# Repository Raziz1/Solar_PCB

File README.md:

# Solar Power Management PCB ☀️
The following project is a power management PCB designed to charge a lithium-ion battery using a solar panel and discharge it into an Arduino for low-power applications.

<p align="center"><i>Blender Render</i></p>

## Arduino Low-Power Application 🔋
Before diving into the PCB design I am going to explore the low-power application that I have designed for this project. The application [Full_Functionality.ino](./Arduino_Code/Full_Functionality/Full_Functionality.ino) utilizes the [DHT11 sensor](https://www.arduino.cc/reference/en/libraries/dht11/) to record temperature and humidity readings, then writes them to the onboard EEPROM (1 KB). Once the data has been stored in the EEPROM the arduino goes into a lower power state by utilizing the [narcoleptic library](https://github.com/brabl2/narcoleptic). I am running this entire application on an [Arduino Uno REV3](https://docs.arduino.cc/hardware/uno-rev3/#tech-specs).

For this application, I would like the Arduino to last as long as possible on battery power. To reduce it's power consumption I referenced the following two articles: [The Arduino Guide to Low Power Design](https://docs.arduino.cc/learn/electronics/low-power/), [Arduino minimal power usage](https://arduino.stackexchange.com/questions/21616/arduino-minimal-power-usage), and [Power saving techniques for microprocessors
](https://www.gammon.com.au/power). A lot of the common techniques involved disabling unused peripherals, reducing clock speeds, and forcing the CPU into a low power mode. One extremely effective method that <b>I did not</b> attempt was utilizing a "bare bones" Atmega328 board. By stripping away a lot of unnecessary components (i.e. USB controller, LDO, etc...) you can significantly reduce the power consumption.

## Arduino Pin-out

| **Arduino** | **DHT11** |
| ------------- | ------------- |
| 5V            | VCC           | 
| GND           | GND           |   
| 2/PD2         | DATA          | 

<br>

<p align="center"><i>Arduino Pin-out</i></p>

## Power Consumption Tests 🪫
To test the power consumption of the Arduino, I used a bench power supply, a 100-ohm shunt resistor, and the Analog Discovery 2 USB oscilloscope.

### Default Sketch
For the first test I had the Arduino running the default sketch as seen below.
```C++
void setup () {}
void loop () {}
```
The current consumption was measured at two supply voltage levels: 12V and 8V. Realistically, for our application, we will be running the Arduino off 8V through the barrel connector.
* 12V - 44.17mA
* 8V - 25.07mA

<p align="center"><i>Current Draw 12V [LEFT] vs 8V [RIGHT]</i></p>

### Low_Power_Sketch.ino
The Low_Power_Sketch.ino utilizes the sleep, wdt, and power library to lower the Arduino's power consumption. To lower the Arduino's power consumption I did the following:

* Desoldered the 5V 'ON' LED
* Disabled USER LED 13
* Disabled ADC
* Changing the clock pre-scalar had no effect on the power consumption so I left it as 1.
* Disabled all peripheral modules (SERIAL, ADC, SPI, USART, TIMER 0, TIMER 1, TIMER 2, I2C)
* Disabled brown-out feature. Brownout detection is a hardware feature that shuts down the processor if the system voltage is below a threshold
* Put the CPU into [SLEEP_MODE_PWR_DOWN](https://onlinedocs.microchip.com/pr/GUID-A834D554-5741-41A3-B5E1-35ED7CD8250A-en-US-5/index.html?GUID-825A28EE-C4E4-4C03-864F-92AA9BA41231). The Microchip web page explains what occurs during this mode.

The resulting current consumptions was:
* 8V - 18.78mA

<p align="center"><i>Current Draw Low_Power_Sketch.ino</i></p>

### Narcoleptic_Sketch.ino
The Narcoleptic_Sketch.ino uses many of the same techniques as the above sketch; however, this script utilizes the [Narcoleptic library](https://github.com/brabl2/narcoleptic) to achieve its low power consumption. The following techniques were used:

* Desoldered the 5V 'ON' LED
* Disabled USER LED 13
* Disabled ADC
* Changing the clock pre-scalar had no effect on the power consumption so I left it as 1.
* Disabled all peripheral modules (SERIAL, ADC, SPI, USART, TIMER 0, TIMER 1, TIMER 2, I2C)
* Disabled brown-out feature. Brownout detection is a hardware feature that shuts down the processor if the system voltage is below a threshold
* Narcoleptic.Delay(x_milliseconds) is called to force the CPU in a low-power state for x_milliseconds.

The resulting current consumptions was:
* 8V - 18.27mA

<p align="center"><i>Current Draw Narcoleptic_Sketch.ino</i></p>

### Full_Functionality.ino
The Full_Functionality.ino sketch is the main program that performs the tasks described in the introduction while using the low power modes that were used in Narcoleptic_Sketch.ino. 

The resulting current consumptions was:
* Awake mode (8V) - 22.42mA
* Low power mode (8V) - 18.30mA

<p align="center"><i>Full_Functionality.ino Low power mode [LEFT] vs Awake mode [RIGHT]</i></p>

### Future Power Consumption Improvements
Despite the power savings documented above, there are still quite a few methods that were left out during this process, which can yield large power savings.

* The first method is extensively discussed in the [Power saving techniques for microprocessors](https://www.gammon.com.au/power) article. You can strip various unnecessary parts from the Arduino, leaving you with a bare-bones version of the board. This includes the voltage regulators (for +5V and +3.3V), USB interface chip (for the USB port), and the "power" LED. According to the article, this resulted in a current consumption of 360uA!
    * The Arduino Uno Rev 3 uses the NCP1117ST50T3G as it's 5V linear voltage regulator. This regulator has a quiescent current of 10mA! If you bypass the LDO you can avoid wasting power.
* Secondly, the ATmega328P MCU can be run at lower frequencies and hence a lower voltage which can reduce the boards power consumption

## Power Management Components ⚡
Now that we know the power consumption of the Arduino, we can begin picking components for this project. This section will focus on the choice of solar panel and lithium-ion battery.

### Lithium Ion Battery 🔋
For the battery, I ended up selecting a pair of lithium-ion batteries I already had at home. The batteries were two 3.7V 2600mAh lithium-ion batteries from PKCELL. The batteries were arranged in series in a battery pack to produce an output voltage of 7.4V and a capacity of 2600 mAh. [Li-ion Battery ICR18650 2600mAh 3.7V Datasheet](https://www.parts-express.com/pedocs/specs/142-202--pkcell-flat-top-18650-li-ion-3.7v-2600mah-rechargeable-battery-spec-sheet.pdf). Some important specifications to note about this battery are the following:
* Nominal Voltage - 3.7V
* Charging Cut-off Voltage - 4.2V
* Discharge Cut-off Voltage - 3.0V
* Standard Charge - Constant Current 0.5C Constant Voltage 4.2V 0.01 C cut-off
* Standard Discharge - Discharge at 0.2 C to 3.0V

<p align="center"><i>PKCELL Lithium Ion Batteries</i></p>

#### Arduino Low-Power Application Discharge Rate
Now that we know the battery capacity and the Arduino's current consumption, we can determine the lifespan of the battery while supplying the Arduino.

| **Variable**  | **Description**           | **Value** |
| ------------- | -------------             | --------- |
| C             | Battery Capacity          | 2600 mAh  | 
| Is            | Current while sleeping    | 18.3mA    |
| Ia            | Current while awake       | 22.4mA    |
| Wph           | # of wakeups per hour     | 1         |
| Wt            | Duration of a single wake | 1s        |

Time awake per hour: ${Twph=Wph\cdot Wt=1s}$

Time asleep per hour: ${Tsph=msph-Wtph=3599s}$

Average current draw: ${Iavg=\left(\left(Ia\cdot Twph\right)+\left(Is\cdot Tsph\right)\right)/3600s=18.3011\thinspace mA}$

Life of battery: ${\frac{C}{I_{avg}}=\frac{2600mAh}{18.3011mA}=142.067\thinspace hours=5.919\thinspace days}$

Alternatively, you could use this [Battery Life Calculator](https://oregonembedded.com/batterycalc.htm), which includes the self-discharge rate of a battery in its calculations. Based on this calculator, the battery's life ends up being 5.03 days.

### Solar Panel 🔆
To increase the lifespan of the battery, you could further decrease the current consumption of the Arduino using the previously mentioned methods, or you could hook up a solar panel to recharge the batteries.

After a bit of searching I was able to find a 12V 4.2W (350mA Max) portable [solar panel module](https://www.amazon.ca/Portable-Polysilicon-Battery-Charger-Efficiency/dp/B07S1P67HL/ref=sr_1_97_sspa?crid=2WAO18NW0X2GN&dib=eyJ2IjoiMSJ9.fZVIoLELaw3YZhhkogK5VGuvzYc6wwH_Px50gEwUL5AK6Nxr_yeX3NtH-g3Q1hlIK30yAnZ0evMQHhDVoLYAm4sbS6SBN7zU1qKFeF3U7BU.zWxxjvWhspQamoYMqpsdiUn7VfXNYG4ixH8fwb_Tuoc&dib_tag=se&keywords=solar+cell&qid=1717475335&s=hi&sprefix=solar+ceil%2Ctools%2C96&sr=1-97-spons&sp_csd=d2lkZ2V0TmFtZT1zcF9hdGZfbmV4dA&psc=1).

#### Ideal Conditions
If we assume ideal conditions where the sun is visible 100% of the day we can determine how long it would take for the solar panel to recharge the battery. 
* ${t}$ is the time (in hours) it takes to charge the battery
* ${Q}$ is the capacity of the battery (in mAh), which is 2600mAh in our case
* ${I}$ is the current (in mA) that the panel can supply, which in our case is 350mA max.

${t=\frac{Q}{I}=\frac{2600}{350}=7.42\thinspace hours}$

#### Real World Conditions
For real-world conditions, we can assume that the total hourly power is closer to 50% of the solar panel's maximum power (175mA). Additionally, we can include the power consumption of the Arduino, which is around 18.3mA.
* ${t}$ is the time (in hours) it takes to charge the battery
* ${Q}$ is the capacity of the battery (in mAh), which is 2600mAh in our case
* ${Iload}$ is the net current (in mA) that the Arduino is drawing, which is 18.3mA in our case
* ${Isolar}$ is the net current (in mA) that the solar panel is providing, which is 175mA in our case. 

${I_{net}=I_{solar}-I_{net}=175\thinspace mA-18.3\thinspace mA=156.7\thinspace mA}$

${t=\frac{Q}{I_{net}}=\frac{2600}{156.7}=16.6\thinspace hours}$

## Battery Management IC 🔌
The battery management IC being used in this project is the [LT3652](https://www.analog.com/en/products/lt3652.html)

* The LT3652 is a complete monolithic step-down battery charger designed for solar power and capable of supporting multi-chemistry, multi-cell batteries.
* Input Supply Voltage Regulation Loop for MPPT Solar Applications
* Wide Input Voltage Range: 4.95V to 32V (40V Abs Max)
* Programmable Charge Rate: Up to 2A
* User-Selectable Termination: C/10 or On-Board Termination Timer
* Resistor Programmable Float Voltage: Up to 14.4V
* Accommodates Li-Ion/Polymer, LiFePO4, SLA Chemistries
* The primary reason for choosing this IC was because a simulation model for it is available in LTspice.

## Design Notes
- [x] VIN Input Supply
- [x] Charge Current Programming
- [x] BOOST Supply
- [x] VIN/BOOST Start-Up Requirement
- [x] VBAT Output Decoupling
- [x] Inductor Selection
- [x] Rectifier Selection
- [x] Battery Float Voltage Programming
- [x] Input Supply Voltage Regulation
- [x] Battery Voltage Temperature Compensation
- [x] Status Pins
- [x] C/10 Termination

### VIN Input Supply
* A high-quality, low ESR decoupling capacitor is recommended to minimize voltage glitches on VIN

#### RMS Ripple Current
${I_{CVIN\left(RMS\right)}≅I_{CHG\left(MAX\right)}•\left(V_{BAT}/V_{IN}\right)•\left(\left[V_{IN}/V_{BAT}\right]-1\right)^{\frac{1}{2}}}$

${I_{CVIN\left(RMS\right)}=0.5\cdot \left(\frac{7.4}{12}\right)\cdot \left(\left(\frac{12}{7.4}\right)-1\right)^{\frac{1}{2}}=0.19447\thinspace A}$

* where ${I_{CHG\left(MAX\right)}}$ is the maximum average charge current
(100mV/ ${R_{SENSE}}$ ).
* The simple worst-case of ½ • ${I_{CHG\left(MAX\right)}}$ is commonly
used for design.
* Ripple current in capacitors is crucial to consider because it directly impacts the component's performance, reliability, and lifespan by causing internal heating and potential degradation

#### Input Ripple Voltage
Bulk capacitance is a function of desired input ripple voltage (ΔVIN), and follows the relation:
${C_{IN{\left(BULK\right)}}=I_{CHG{\left(MAX\right)}}•\left(V_{BAT}/V_{IN}\right)/∆V_{IN}\thinspace \left(µF\right)}$

${C_{IN\left(BULK\right)}=0.4\cdot \frac{\left(\frac{7.4}{12}\right)}{0.1}=2.46\thinspace uF}$

* Input ripple voltages above 0.1V are not recommended. 10µF is typically adequate for most charger applications.

### Charge Current Programming
The data sheet describes the charge current programming as follows: <i>"The LT3652 charger is configurable to charge at average currents as high as 2A. Maximum charge current is set by choosing an inductor sense resistor (RSENSE)..."</i> 

${R_{SENSE}\thinspace = \thinspace 0.1/I_{CHG\left(MAX\right)}}$

The maximum charging current is limited by the maximum current output of the solar panel, which is 350 mA. Therefore, we can set the limit to 400 mA to allow for some headroom.

${R_{SENSE}\thinspace = \thinspace 0.1/I_{CHG\left(MAX\right)}=0.1/0.4=0.25Ω}$

### BOOST Supply
The voltage on the decoupling capacitor is refreshed through a diode, with the anode connected to either the battery output voltage or an external source, and the cathode connected to the BOOST pin. Rate the diode average current greater than 0.1A, and reverse voltage greater than VIN(MAX).

### VIN/BOOST Start-Up Requirement
When an LT3652 charger is not switching, the SW pin is
at the same potential as the battery, which can be as high
as VBAT(FLT). As such, for reliable start-up, the VIN supply
must be at least 3.3V above VBAT(FLT). Once switching
begins and the BOOST supply capacitor gets charged
such that (VBOOST – VSW) > 2V, the VIN requirement no
longer applies.

### VBAT Output Decoupling
An LT3652 charger output requires bypass capacitance connected from the BAT pin to ground (CBAT). A 10µF ceramic capacitor is required for all applications.
* If it is desired to operate a system load from the LT3652 charger output when the battery is disconnected, additional bypass capacitance is required. In this type of application, excessive ripple and/or low amplitude oscillations can occur without additional output bulk capacitance. For these applications, place a 100µF low ESR non-ceramic capacitor (chip tantalum or organic semiconductor capacitors such as Sanyo OS-CONs or POSCAPs) from BAT to ground, in parallel with the 10µF ceramic bypass capacitor. This additional bypass capacitance may also be required in systems where the battery is connected to the charger with long wires. The voltage rating of CBAT must meet or exceed the battery float voltage.

### Inductor Selection
The primary criterion for inductor value selection in an LT3652 charger is the ripple current created in that inductor.
* Once the inductance value is determined, an inductor must also have a saturation current equal to or exceeding the maximum peak current in the inductor
* ${L=\frac{10•R_{SENSE}}{\frac{ΔI_L}{I_{CHG\left(MAX\right)}}}•V_{BAT\left(FLT\right)}•\left(1-\frac{V_{BAT\left(FLT\right)}}{V_{IN\left(MAX\right)}}\right)\thinspace \left(µH\right)}$
    * ${L=\frac{10\cdot 0.2}{\frac{0.12}{0.4}}\cdot 7.4\cdot \left(1-\frac{7.4}{12}\right)=23.64\thinspace uH}$    
* In the above relation, VIN(MAX) is the maximum operational voltage. Ripple current is typically set within a range of 25% to 35% of ICHG(MAX), so an inductor value can be determined by setting 0.25 < ΔIL/ICHG(MAX) < 0.35
* Magnetics vendors typically specify inductors with maximum RMS and saturation current ratings. Select an inductor that has a saturation current rating at or above ${\left(1+ΔI_{MAX}/2\right)•I_{CHG\left(MAX\right)}}$, and an RMS rating above ${I_{CHG\left(MAX\right)}}$.
* Inductors must also meet a maximum voltsecond product requirement. If this specification is not in the data sheet of an inductor, consult the vendor to make sure the maximum volt-second product is not being exceeded by your design. The minimum required volt-second product is: ${V_{BAT\left(FLT\right)}•\left(\frac{1-V_{BAT\left(FLT\right)}}{V_{IN\left(MAX\right)}}\right)\left(V•\thinspace µS\right)}$

### Rectifier Selection
The rectifier diode from SW to GND, in a LT3652 battery charger provides a current path for the inductor current when the main power switch is disabled. The rectifier is selected based upon forward voltage, reverse voltage, and maximum current. A Schottky diode is required, as low forward voltage yields the lowest power loss and highest efficiency. The rectifier diode must be rated to withstand reverse voltages greater than the maximum VIN voltage.

The minimum average diode current rating (${I_{DIODE\left(MAX\right)}}$)
is calculated with maximum output current (${I_{CHG\left(MAX\right)}}$),
maximum operational VIN, and output at the precondition
threshold (${V_{BAT\left(PRE\right)},\thinspace or\thinspace 0.7•V_{BAT\left(FLT\right)}}$): ${I_{DIODE\left(MAX\right)}>I_{CHG\left(MAX\right)}•\frac{V_{IN\left(MAX\right)}-V_{BAT\left(PRE\right)}}{V_{IN\left(MAX\right)}}\left(A\right)}$

${I_{DIODE\left(MAX\right)}>0.4\cdot \frac{12-5.18}{12}}$

${I_{DIODE\left(MAX\right)}>0.2273\thinspace A}$

### Battery Float Voltage Programming
The output battery float voltage (VBAT(FLT)) is programmed by connecting a resistor divider from the BAT pin to VFB. VBAT(FLT) can be programmed up to 14.4V.

Using a resistor divider with an equivalent input resistance at the VFB pin of 250k compensates for input bias current error. Required resistor values to program desired VBAT(FLT) follow the equations:
* ${R_{FB1}=\left(V_{BAT\left(FLT\right)}•2.5•10^5\right)/3.3\thinspace \left(Ω\right)}$
* ${R_{FB2}=\left(R_{FB1}•\left(2.5•10^5\right)\right)/\left(R_{FB1}-\left(2.5•10^5\right)\right)\thinspace \left(Ω\right)}$ 

The charge function operates to achieve the final float voltage of 3.3V on the VFB pin. The auto-restart feature initiates a new charging cycle when the voltage at the VFB pin falls 2.5% below that float voltage. Because the battery voltage is across the VBAT(FLT) programming resistor divider, this divider will draw a small amount of current from the battery (IRFB) at a rate of: IRFB = 3.3/RFB2

Precision resistors in high values may be hard to obtain, so for some lower VBAT(FLT) applications, it may be desirable to use smaller-value feedback resistors with an additional resistor (RFB3) to achieve the required 250k equivalent resistance. The resulting 3-resistor network, as shown in Figure 5, can ease component selection and/or increase output voltage precision, at the expense of additional current through the feedback divider.

${\frac{R_{FB2}}{R_{FB1}}=\frac{3.3}{\left(V_{BAT\left(FLT\right)}-3.3\right)}}$

${\frac{R_{FB2}}{R_{FB1}}=\frac{3.3}{\left(7.4-3.3\right)}=0.80487}$

Set the divider current (IRFB) = 10uA yields:

${R_{FB2}=\frac{3.3}{10uA}=330k}$

Solving for RFB1:

${R_{FB1}=\frac{330k}{0.80487}=410k}$

The divider equivalent resistance is:

${R_{FB1}||R_{FB2}=182.8k}$

To satisfy the 250k equivalent resistance to the VFB pin: 

${R_{FB3}=250k-182.8k=67.2k}$

Because the VFB pin is a relatively high impedance node, stray capacitances at this pin must be minimized. Special attention should be given to any stray capacitances that
can couple external signals onto the pin, which can produce undesirable output transients or ripple. Effects of parasitic capacitance can typically be reduced by adding
a small-value (20pF to 50pF) feed forward capacitor from the BAT pin to the VFB pin

### Input Supply Voltage Regulation

The LT3652 contains a voltage monitor pin that enables programming a minimum operational voltage. Connecting a resistor divider from VIN to the VIN_REG pin enables programming of minimum input supply voltage, typically used to program the peak power voltage for a solar panel. Maximum charge current is reduced when the VIN_REG pin is below the regulation threshold of 2.7V. If an input supply cannot provide enough power to satisfy
the requirements of an LT3652 charger, the supply voltage will collapse. A minimum operating supply voltage can thus be programmed by monitoring the supply through a resistor divider, such that the desired minimum voltage corresponds to 2.7V at the VIN_REG pin. The LT3652 servos the maximum output charge current to maintain
the voltage on VIN_REG at or above 2.7V. Programming of the desired minimum voltage is accomplished by connecting a resistor divider as shown in
Figure 6. The ratio of RIN1/RIN2 for a desired minimum voltage (VIN(MIN)) is:

${\frac{R_{IN1}}{R_{IN2}}=\left(\frac{V_{IN\left(MIN\right)}}{2.7}\right)-1}$

If the voltage regulation feature is not used, connect the VIN_REG pin to VIN.

For my configuration I will set the ${V_{IN\left(MIN\right)}}$ as 10V 

${\frac{R_{IN1}}{R_{IN2}}=\frac{10}{2.7}-1=2.7037}$

${R_{IN1}=270k}$

${R_{IN2}=100k}$

### MPPT Temperature Compensation

### Battery Voltage Temperature Compensation

<i>See Page 16 of the datasheet for MPPT temperature compensation and battery voltage temperature compensation</i>

In this design I opted to ignore the following features to simplify the design. Nevertheless, these features are actually very easy to work with and are well documented within the datasheet.

### Status Pins

The LT3652 reports charger status through two open collector outputs, the CHRG and FAULT pins. These pins can accept voltages as high as VIN, and can sink up to 10mA when enabled. The CHRG pin indicates that the charger is delivering current at greater that a C/10 rate, or 1/10th of the programmed maximum charge current. The FAULT pin signals bad battery and NTC faults.

If the battery is removed from an LT3652 charger that is configured for C/10 termination, a sawtooth waveform of approximately 100mV appears at the charger output, due to cycling between termination and recharge events, This cycling results in pulsing at the CHRG output. An LED connected to this pin will exhibit a blinking pattern, indicating to the user that a battery is not present. The frequency of this blinking pattern is dependent on the output capacitance.

<p align="center"><i>Status Pins Table</i></p>

### C/10 Termination

The LT3652 supports a low-current based termination scheme, where a battery charge cycle terminates when the current output from the charger falls to below one-tenth of the maximum current, as programmed with RSENSE. The C/10 threshold current corresponds to 10mV across RSENSE. This termination mode is engaged by shorting the TIMER pin to ground.
When C/10 termination is used, a LT3652 charger will source battery charge current as long as the average current level remains above the C/10 threshold. As the full-charge float voltage is achieved, the charge current falls until the C/10 threshold is reached, at which time the charger terminates and the LT3652 enters standby mode. The CHRG status pin follows the charger cycle, and is high impedance when the charger is not actively charging. When VBAT drops below 97.5% of the full-charged float voltage, whether by battery loading or replacement of the battery, the charger automatically re-engages and starts charging. There is no provision for bad battery detection if C/10 termination is used.

## Thermal Consideration 🔥
A schottky diode is placed at the output of a solar panel primarily to prevent reverse current flow, which can discharge the battery at night or during low-light conditions. For this schottky diode I had originally chosen the [B5817WS-TP](https://www.digikey.com/en/products/detail/micro-commercial-co/B5817WS-TP/2213553). One thing to consider is the thermal performance of this diode. 

According to the datasheet, we expect this to operate with an average forward voltage drop of 0.45V. We also expect it to sink 350mA at the solar panel's peak performance.

${P=V\cdot I=0.45\cdot 0.350=0.1575\ Watts}$

According to the datasheet the maximum thermal resistance is 500°C/W from junction to ambient. Therefore we would expect the diode to rise above ambient temperature by:

${T=500°C/W\cdot 0.1575W=78.75°C}$

While this is technically within the operating specifications of the diode, it would be wise to consider a diode with superior thermal performance to prevent potential thermal runaway.

As such, a suitable alternative with a slightly larger case size would be the [SMD22PL-TP](https://www.digikey.ca/en/products/detail/micro-commercial-co/SMD22PL-TP/1793265). By using the same calculations as above, we can expect the following power dissipation:

${P=V\cdot I=0.5\cdot 0.350=0.175\ Watts}$

${T=115°C/W\cdot 0.175W=20.125°C}$

## Simulation

<p align="center"><i>LTSpice Schematic Capture</i></p>

<p align="center"><i>LTSpice Charge Simulation 0% --> 100% (Vin vs Vout)</i></p>

<p align="center"><i>LTSpice CHG LED Status</i></p>

### Layout Considerations
* The switch node (Pin SW) trace should be kept as short as possible to minimize high frequency noise.
* The input capacitor (CIN) should be placed close to the IC to minimize this switching noise.
* Short, wide traces on these nodes also help to avoid voltage stress from inductive ringing.
* The BOOST decoupling capacitor should also be in close proximity to the IC to minimize inductive ringing.
* The SENSE and BAT traces should be routed together, and these and the VFB trace should be kept as short as possible. Shielding these signals from switching noise with a ground plane is recommended.
* High current paths and transients should be kept isolated from battery ground, to assure an accurate output voltage reference.
* The LT3652 packaging has been designed to efficiently remove heat from the IC via the Exposed Pad on the backside of the package, which is soldered to a copper footprint on the PCB. This footprint should be made as large as possible to reduce the thermal resistance of the IC case to ambient air.

<p align="center"><i>Layout power loops</i></p>

## PCB Design

<p align="center"><i>Schematic Design</i></p>

<p align="center"><i>PCB Design</i></p>

### Design Choices
* I have incorporated 6 vias beneath the ground pad of the LT3652, connecting to the bottom layer ground plane. This design choice aims to improve thermal dissipation by effectively transferring heat away from the chip and to the lower ground plane.
* I have placed grounded via stitching all along the edge of the board to achieve multiple benefits: reducing electromagnetic emissions by containing radially propagating waves, improving shielding to protect internal circuitry from external interference, and enhancing ground connectivity by linking ground planes across different layers, thereby ensuring efficient current return paths and low impedance. 
* Via stitching has been strategically applied around traces and components associated with high-frequency switching nodes, along with sensitive feedback lines. This technique is known as shielding and helps prevent the coupling of EM waves into stray traces in two ways: The loop inductance in the via region is lower because the via is closer to ground. Being closer to ground causes the signal via/ground via transition to dominate the total capacitance experienced along the via. 
    * You can calculate the maximum frequency that a given array of stitching vias will shield against based on their spacing. ${f_{max}=\frac{c}{8\cdot \:s\cdot \sqrt{ε_r}}=\frac{299792458}{8\:\cdot \:0.002\cdot \sqrt{4.4}}=8.93GHz}$
        * (c) - The speed of light 299792458 m/s
        * (s) - The spacing between Via's
        * (ε) - relative permittivity (εr) of the PCB material. For FR-4 ≈ 4.4

<p align="center"><i>Layout power loops</i></p>

## Final BOM 📃
* 2× [ICR18650 2600mAh 3.7V by PKCELL](https://www.batterypkcell.com/pkcell-18650-3-7v-2200mah-new-rechargeable-lithium-battery-product/)
* [12V 4.2W Solar Panel Module](https://www.amazon.ca/Portable-Polysilicon-Battery-Charger-Efficiency/dp/B07S1P67HL/ref=sr_1_97_sspa?crid=2WAO18NW0X2GN&dib=eyJ2IjoiMSJ9.fZVIoLELaw3YZhhkogK5VGuvzYc6wwH_Px50gEwUL5AK6Nxr_yeX3NtH-g3Q1hlIK30yAnZ0evMQHhDVoLYAm4sbS6SBN7zU1qKFeF3U7BU.zWxxjvWhspQamoYMqpsdiUn7VfXNYG4ixH8fwb_Tuoc&dib_tag=se&keywords=solar+cell&qid=1717475335&s=hi&sprefix=solar+ceil%2Ctools%2C96&sr=1-97-spons&sp_csd=d2lkZ2V0TmFtZT1zcF9hdGZfbmV4dA&psc=1)
* [Renogy 10 Watt 12 Volt Monocrystalline Solar Panel](https://www.amazon.ca/Renogy-Monocrystalline-Compact-Sprinkler-Applications/dp/B084MGS7KC/ref=mp_s_a_1_3?dib=eyJ2IjoiMSJ9.c6Ibopwzdw26-vXq0iM-t1X8KARw0PDHBEDa3QlSnucRRHnDQTm4tTqQhkWwJL5nBQfEcQG8s4SG3f0IUzD3oGxv7BOgHw_WdngOzWXWF6KB_JtXohbMmgxpaDqCVNrzySHuhJVVXBAElseQOjCSJATDCa9YTwj-vGisQsCN-2uRbedcTW2VFvSyFnXtX7MV--3pARRPw2olqf5FF4tQuw.rWuqIR5JHi2lb0LAExF7YcRQJTtzPzDO3Edo9STDuG8&dib_tag=se&keywords=10%2Bwatt%2Bsolar%2Bpanel&qid=1720388517&sr=8-3&th=1) (More powerful solar panel alternative)
    * [Datasheet](https://ca.renogy.com/content/renogy-day-2023/RNG-10D-SS-G1Datasheet.pdf)
    * Optimum Operating Voltage - 18V
    * Optimum Operating Current - 0.56A
* [LT3652EMSE#TRPBF - IC BATT CHG MULTI-CHEM 12MSOP](https://www.digikey.ca/en/products/detail/analog-devices-inc/LT3652EMSE-TRPBF/7838158)
* 1× [B5817WS-TP - DIODE SCHOTTKY 20V 1A SOD323](https://www.digikey.com/en/products/detail/micro-commercial-co/B5817WS-TP/2213553)
* 1× [SS2P2-M3/84A - Diode 20 V 2A Surface Mount DO-220AA (SMP)](https://www.digikey.ca/en/products/detail/vishay-general-semiconductor-diodes-division/SS2P2-M3-84A/1091548)
* 1× [MBRS340T3G - DIODE SCHOTTKY 40V 3A SMC](https://www.digikey.com/en/products/detail/onsemi/MBRS340T3G/918009)
* 2× [150060VS75000 - LED GREEN CLEAR 0603 SMD](https://www.digikey.ca/en/products/detail/w%C3%BCrth-elektronik/150060VS75000/4489906)
* 2× [ERJ-3EKF1101V - RES SMD 1.1K OHM 1% 1/10W 0603](https://www.digikey.ca/en/products/detail/panasonic-electronic-components/ERJ-3EKF1101V/196037)
* 2× [CL10A106MA8NRNC - CAP CER 10UF 25V X5R 0603](https://www.digikey.ca/en/products/detail/samsung-electro-mechanics/CL10A106MA8NRNC/3887527)
* 2× [CL10A105KA8NNNC - CAP CER 1UF 25V X5R 0603](https://www.digikey.ca/en/products/detail/samsung-electro-mechanics/CL10A105KA8NNNC/3886760)
* [RL0603FR-070R25L - RES 0.25 OHM 1% 1/10W 0603](https://www.digikey.ca/en/products/detail/yageo/RL0603FR-070R25L/5924891)
* [7447798241 - FIXED IND 24UH 4.5A 39.5MOHM SMD](https://www.digikey.ca/en/products/detail/w%C3%BCrth-elektronik/7447798241/2268621)
* [RC0603FR-07412KL - RES 412K OHM 1% 1/10W 0603](https://www.digikey.ca/en/products/detail/yageo/RC0603FR-07412KL/727227)
* [ERJ-3EKF3303V - RES SMD 330K OHM 1% 1/10W 0603](https://www.digikey.ca/en/products/detail/panasonic-electronic-components/ERJ-3EKF3303V/1746380)
* [ERJ-3EKF6802V - RES SMD 68K OHM 1% 1/10W 0603](https://www.digikey.ca/en/products/detail/panasonic-electronic-components/ERJ-3EKF6802V/1746444)
* [ERJ-3EKF1003V - RES SMD 100K OHM 1% 1/10W 0603](https://www.digikey.ca/en/products/detail/panasonic-electronic-components/ERJ-3EKF1003V/196075)
* [ERJ-3EKF2703V - RES SMD 270K OHM 1% 1/10W 0603](https://www.digikey.ca/en/products/detail/panasonic-electronic-components/ERJ-3EKF2703V/1746359)

## Manufacturing 🪛
I ordered the board through PCBWay by using the [KiCAD plugin](https://www.pcbway.com/blog/News/PCBWay_Plug_In_for_KiCad_3ea6219c.html). I assembled and soldered the components on the board myself. 

For the PCBWay specification selection I chose the following options:
* Layers: 2
* Material: FR-4
* FR4-TG: TG130-140
* Thickness: 1.6mm
* Min track/spacing: 5/5mil
* Solder mask: Red
* Silkscreen: White
* Edge connector: No
* Surface finish: HASL with lead
* Via process: Tenting vias
* Finished copper: 1 oz Cu
* Remove product Num: No

<p align="center"><i>Final Product</i></p>

## Characterization 🔬
Finally, I wanted to characterize the response of the circuit using my Analog Discovery 2 - USB oscilloscope. For my initial test setup, I connected the power input of the PCB to a power supply, configuring it to deliver 12V while limiting the current to 300mA. Additionally, I connected a pair of lithium-ion batteries to the PCB, which were discharged to approximately 7V.

### Efficiency 📈
To assess the circuit's output efficiency, I conducted the following calculations based on the input and output power.

#### Input
${P=V\cdot I=12V\cdot 0.275A=3.3W}$

#### Output
${P=V\cdot I=7.4\cdot 0.403A=2.9822W}$

${
\text{Efficiency} = \frac{P_{\text{out}}}{P_{\text{in}}} \cdot 100 = \frac{2.9822}{3.3} \cdot 100 = 0.9036 \cdot 100 = 90.4\\%
}$

<p align="center"><i>Input Power</i></p>

<p align="center"><i>Output Current</i></p>

### Thermal Imaging 🔥
I had the opportunity to conduct thermal imaging on the PCB during its operation by utilizing a FLIR thermal camera. As shown in the image, the primary hotspots were the input diode, battery management IC, and LED indicators. After approximately five minutes of operation at room temperature, the system began to stabilize, with peak temperatures reaching 52.4 degrees Celsius.

<p align="center"><i>Thermal Image</i></p>

### Output Voltage
The output voltage is well-centered around 7.4V, and the signal is generally acceptable. However, there are a few important observations to consider. First, there are ringing transients at the beginning of each recovery cycle of the converter. Second, the output ripple voltage is approximately 80mV. While this is within an acceptable range, it is slightly higher than desired. To reduce the output voltage ripple in a buck converter, consider selecting inductors with low parasitic capacitance and appropriate inductance values. Additionally, choose output capacitors with low equivalent series resistance (ESR) and equivalent series inductance (ESL). Increasing the output capacitance can also significantly suppress voltage ripple, thereby enhancing overall performance.

<p align="center"><i>Output Voltage</i></p>

### Switching Node
You can observe the switching node in the image below. As specified in the datasheet, the switching frequency is 1 MHz. Furthermore, as mentioned in the previous section, the same ringing transient is evident at both the rising and falling edges of the signal. Ringing on the switching node of a buck converter is primarily caused by parasitic inductances and capacitances. The ringing occurs when the high-side switch turns on, and the energy stored in parasitic inductances is released, interacting with parasitic capacitances to create an LC tank circuit. In boost converters, the critical component regarding ringing is often the boost diode, and its characteristics can significantly influence the ringing behavior. You can do the following to reduce switch node ringing: 
* Adding snubber circuits to dampen the oscillations. 
* Implementing Schottky or Zener clamps to limit voltage spikes.

<p align="center"><i>Switching Node</i></p>

> [!CAUTION]
> To investigate the source of the ringing observed in earlier measurements, I recaptured the switching node waveform using a Tektronix MSO44B oscilloscope with 1.5 GHz bandwidth and 12-bit resolution. In this capture, the ringing was no longer present, which highlighted that the Analog Discovery 2's 10 MHz analog bandwidth was not sufficient to accurately capture the characteristics of fast digital transitions with rise times around 25 ns—as was mentioned by @JoshMuir. Accurately observing such transitions requires significantly higher bandwidth, typically at least three times the frequency content of the fastest signal components. The earlier distortion was likely due to this limitation, along with some stray inductance in the probe setup.

<p align="center"><i>Switching Node on Tektronix MS044B</i></p>

### Solar Test ☀️
For one of my final test setup, I connected the solar panel, lithium-ion battery pack, and Arduino to the PCB, then placed it in the bright sunlight around noon. On that day, a thin layer of clouds softened the sun's rays. I slightly discharged the battery to approximately 6.8V and set the Arduino to operate in a low-power state using the Narcoleptic library. During this time, the solar panel was able to produce 12V at around 172mA. After connecting everything, I turned off the battery switch and measured the current draw of the Arduino by placing a multimeter in series with it. During its low-power sleep mode, the Arduino was drawing 22.7mA of current. This slightly differs from our initial measurements of the Arduino in low-power mode, which can be attributed to minor errors in the measurement instruments. Finally, I turned on the battery switch and allowed the entire system to run. The Arduino remained powered on, executing its software while the battery charged slowly. I measured the current flowing into both the battery and the Arduino by probing the voltage across the 0.25-ohm sense resistor. The voltage drop was 53.2mV, indicating that both were consuming a total of 212.8mA. During full operation, the charge LED was illuminated, indicating that the circuit was functioning correctly and that the batteries were charging.

To assess the circuit's output efficiency during operating, I conducted the following calculations based on the input and output power.

#### Input
${P=V\cdot I=10.21V\cdot 0.172A=1.756W}$

The input voltage from the solar panel was measured at 10.21V instead of the expected 12V, which is attributed to the programmed peak power voltage configured with a voltage divider for the V_In_Reg pin.

#### Output
${P=V\cdot I=7.4\cdot 0.2128A=1.575W}$

${
\text{Efficiency} = \frac{P_{\text{out}}}{P_{\text{in}}} \cdot 100 = \frac{1.575}{1.756} \cdot 100 = 0.896 \cdot 100 = 89.6\\%
}$

<p align="center"><i>Solar Test</i></p>

### Extended Solar Test ☀️
For one of my final test setups, I connected the solar panel, lithium-ion battery pack, and Arduino to the PCB. Then, I connected my Analog Discovery 2 USB oscilloscope to the battery terminals and solar panel terminals. Finally, I taped the solar panel to my room window and began my scope capture at 3 AM. I ran the scope capture from 3 AM to 11:30 PM to characterize the circuit's response during an entire day of sun exposure. On this day, there were clear skies and approximately 12 hours of bright sunshine. The battery was nearly full at the beginning of the test, so throughout the day, minimal charging occurred.

<p align="center"><i>Extended Solar Test</i></p>

<p align="center"><i>Extended Solar Test</i></p>

# Future Considerations
* Characterize battery discharge into Arduino over an entire cell cycle.
* Characterize battery charging from solar cell during an entire charging cycle.
* Fix switch node ringing with a snubber circuit.
* Add reverse polarity protection.
* The Arduino utilizes a 5V Low Dropout (LDO) regulator with a dropout voltage of 200mV. Consequently, if the battery voltage drops below 5.2V, the Arduino will shut down. To address this issue, we can incorporate an intermediary buck-boost converter capable of operating at low input voltages.

# Resources
* [Designing a Solar and Li-ion Battery Powered Charger / Power Source Part 1](https://www.youtube.com/watch?v=NaxtGdHR_6E)
* [The Arduino Guide to Low Power Design](https://docs.arduino.cc/learn/electronics/low-power/)
* [Power saving techniques for microprocessors](https://www.gammon.com.au/power)
* [narcoleptic](https://github.com/brabl2/narcoleptic)
* [How to Permanently Store Data on an Arduino's Built-in EEPROM](https://www.digikey.ca/en/maker/blogs/2021/how-to-permanently-store-data-on-an-arduinos-built-in-eeprom)
* [Switching Regulator PCB Design - Phil's Lab #60](https://www.youtube.com/watch?v=AmfLhT5SntE)
* [Common Mistakes in DC/DC Converters and How to Fix Them](https://login.ti.com/as/authorization.oauth2?response_type=code&scope=openid%20email%20profile&client_id=DCIT_ALL_WWW-PROD&state=H5b-fq0Q4IgyNCEjBbyU4sybOCs&redirect_uri=https%3A%2F%2Fwww.ti.com%2Foidc%2Fredirect_uri%2F&nonce=n3bXoPABEGb6cJAH1qzcaZyaWSE1Pe7WqVE4aP_YNXY&response_mode=form_post)
* [Constructing Your Power SupplyLayout Considerations](http://www.submm.caltech.edu/kids_html/DesignLog/DesignLog179/MillerMUSICReadoutDocs/slup230.pdf)
* [PCBWAY Custom Design Rules Templates](https://www.pcbway.com/pcb_prototype/PCB_Design_Rule_Check.html?currency=1)

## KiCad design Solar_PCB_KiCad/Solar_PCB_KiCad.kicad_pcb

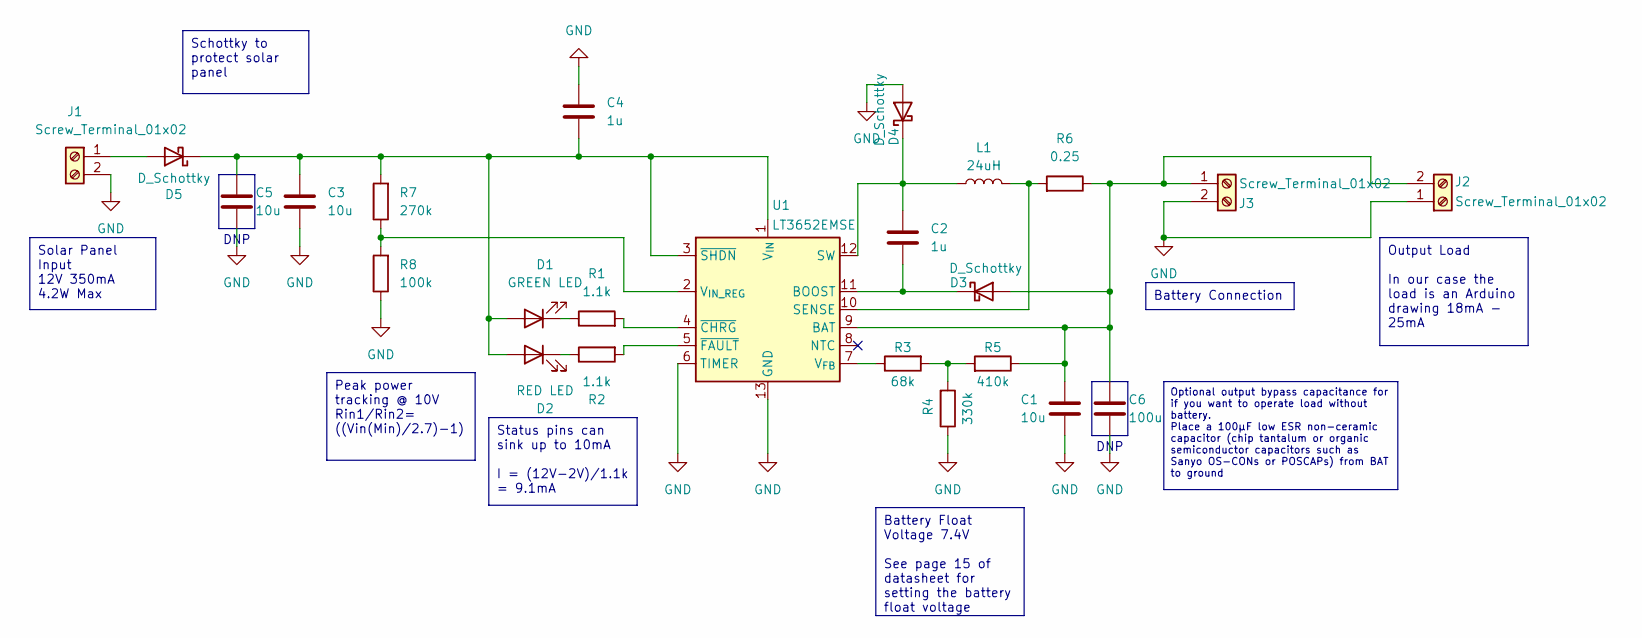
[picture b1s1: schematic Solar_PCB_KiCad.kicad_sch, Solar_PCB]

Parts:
C1, C3, C5: 10u; C_0603_1608Metric
C2, C4: 1u; C_0603_1608Metric
C6: 100u; C_0603_1608Metric
D1: GREEN LED; LED_0603_1608Metric
D2: RED LED; LED_0603_1608Metric
D3: D_Schottky; D_SOD-323
D4: D_Schottky; D_SMC_Handsoldering
D5: D_Schottky; D_SMP_DO-220AA
J1, J2, J3: Screw_Terminal_01x02; TerminalBlock_Phoenix_MKDS-1,5-2-5.08_1x02_P5.08mm_Horizont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
L1: 24uH; L_Wuerth_WE-PDF_Handsoldering
R1, R2: 1.1k; R_0603_1608Metric
R3: 68k; R_0603_1608Metric
R4: 330k; R_0603_1608Metric
R5: 410k; R_0603_1608Metric
R6: 0.25; R_0603_1608Metric
R7: 270k; R_0603_1608Metric
R8: 100k; R_0603_1608Metric
U1: LT3652EMSE; MSOP-12-1EP_3x4mm_P0.65mm_EP1.65x2.85mm

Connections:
GND: C1.2, C3.2, C4.2, C5.2, C6.2, D4.2 (A), J1.2, J2.1, J3.2, R4.1, R8.1, U1.6 (TIMER), U1.13 (GND)
unnamed: C3.1, C4.1, C5.1, D1.2 (A), D2.2 (A), D5.1 (K), R7.2, U1.1 (V_{IN}), U1.3 (~SHDN)
unnamed: D1.1 (K), R1.1
unnamed: D2.1 (K), R2.1
unnamed: C1.1, C6.1, D3.2 (A), J2.2, J3.1, R5.1, R6.1, U1.9 (BAT)
unnamed: C2.2, D3.1 (K), U1.11 (BOOST)
unnamed: C2.1, D4.1 (K), L1.1, U1.12 (SW)
unnamed: D5.2 (A), J1.1
unnamed: R3.2, R4.2, R5.2
unnamed: L1.2, R6.2, U1.10 (SENSE)
unnamed: R3.1, U1.7 (V_{FB})
unnamed: R7.1, R8.2, U1.2 (V_{IN_REG})
unnamed: R1.2, U1.4 (~CHRG)
unnamed: R2.2, U1.5 (~FAULT)

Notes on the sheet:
Output Load In our case the load is an Arduino drawing 18mA - 25mA
Solar Panel Input 12V 350mA 4.2W Max
Status pins can sink up to 10mA I = (12V-2V)/1.1k = 9.1mA
Battery Float Voltage 7.4V See page 15 of datasheet for setting the battery float voltage
Optional output bypass capacitance for if you want to operate load without battery. Place a 100µF low ESR non-ceramic capacitor (chip tantalum or organic semiconductor capacitors such as Sanyo OS-CONs or POSCAPs) from BAT to ground
Schottky to protect solar panel
Peak power tracking @ 10V Rin1/Rin2= ((Vin(Min)/2.7)-1)
Battery Connection
DNP

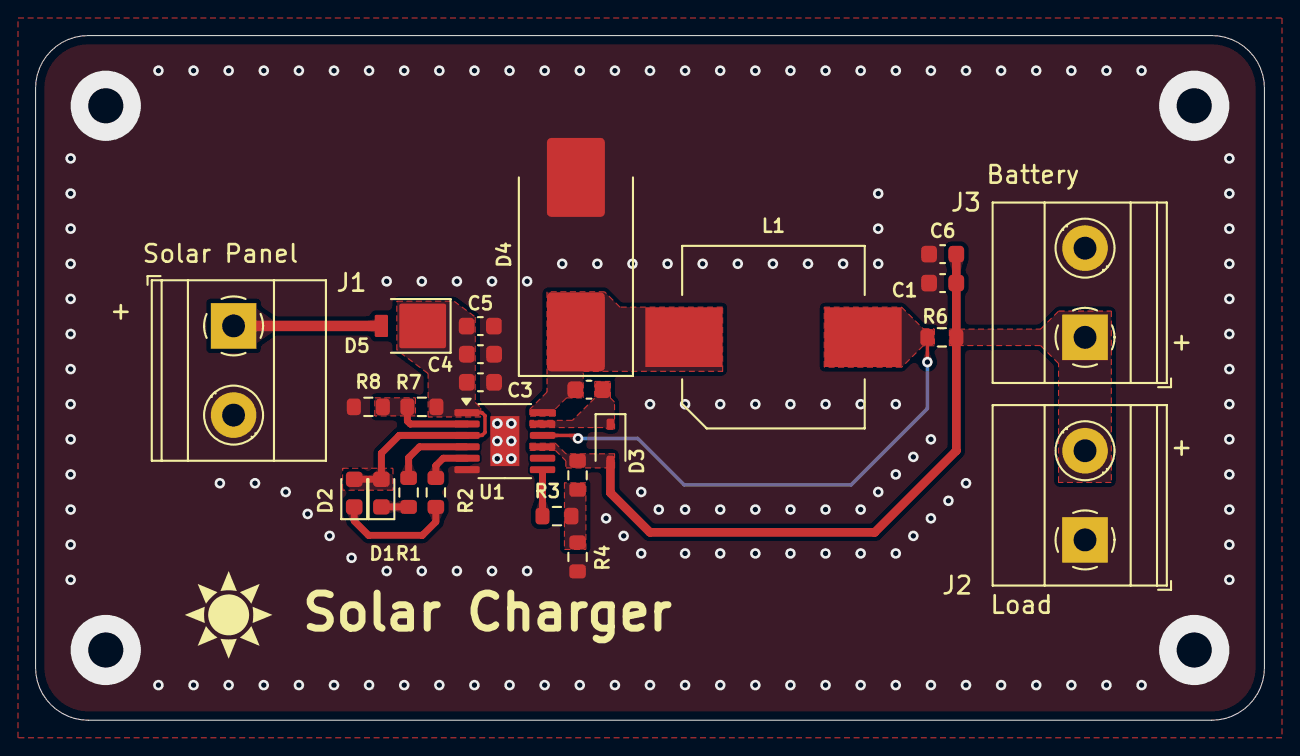
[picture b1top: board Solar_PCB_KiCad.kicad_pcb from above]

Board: 2 copper layers, 70.0 x 39.0 mm, 24 parts (0 on the bottom side), 14 nets.

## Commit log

2024-05-29 Updated Full_Functionality Script
    Now utilizing Narcoleptic library for low power modes
2024-05-29 Updated Arduino Low Power Application section
2024-05-30 Updated arduino low power references
2024-05-31 Power Consumption Test
2024-05-31 Power consumption tests
2024-05-31 Added images
2024-06-04 Updated power consumption
2024-06-04 Updated battery/solar panel calculations
2024-06-04 Updated battery management IC
2024-06-04 LTSpice simulation
2024-06-05 Updated charge current programming
2024-06-08 Updated README File
2024-06-19 Updated battery life calculations
2024-06-21 Updated spice
2024-06-21 KiCad PCB
2024-06-23 Updated calculations
2024-06-23 Updated Schematic
2024-06-23 Updated schematic & PCB
2024-06-23 Updated Schematics
2024-06-28 Updated simulation
2024-06-28 Updated math for charging
2024-07-08 Updated BOM
2024-07-10 Updated KiCad
2024-07-11 Updated Datasheets
2024-07-11 Updated PCB
2024-07-18 Updated PCB Layout
2024-07-19 Updated SIM
2024-07-23 Updated layout & render
2024-07-23 Added grounded mounting holes
2024-07-23 Removed old characterization section
2024-07-24 Updated Layout
2024-07-24 Updated layout considerations
2024-07-25 Updated design choices section
2024-07-25 Updated Via shielding
2024-07-29 Added optional bypass and input capacitance
2024-07-29 Updated thermal consideration section
2024-07-29 Updated render
2024-07-29 Updated images
2024-07-30 Updated diode + render + thermal considerations
2024-07-31 Capacitor ripple current
2024-07-31 Updated resources
2024-08-06 Updated PCBway export
2024-08-06 Updated output files
2024-08-14 Fixed GND net short
    Fixed short between input net and GND by repouring GND polygon
2024-08-14 Updated README.md
    * Added final assembly picture
    * Added output voltage picture
    * Fixed silkscreen
2024-08-15 Updated README formatting
2024-08-19 Updated PCB_Assembly.jpg
2024-08-30 Future considerations
2024-10-19 Added extended solar test graphs
2024-10-19 Updated Code
2025-05-01 Added note about oscilloscope analysis
